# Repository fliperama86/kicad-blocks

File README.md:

# kicad-blocks

Reusable KiCad design blocks shared across projects.

Each subdirectory is a single block: a self-contained schematic snippet
(plus optional layout, symbols, and footprints) that can be dropped into
any KiCad project as a hierarchical sheet or, in KiCad 9+, registered as
a Design Block library.

## Layout

```
kicad-blocks/
├── README.md
├── <block-name>/
│   ├── README.md                  # what the block is, sheet pins, BOM, gotchas
│   ├── <block-name>.kicad_sch     # the reusable schematic
│   ├── <block-name>.kicad_pcb     # optional preplaced layout
│   ├── symbols/                   # block-specific symbol library (.kicad_sym)
│   └── footprints.pretty/         # block-specific footprints (.kicad_mod)
└── ...
```

A block should expose its interface only via hierarchical sheet pins.
Anything internal (decoupling caps, crystal, regulator) stays inside
the sheet so projects can reuse without re-wiring.

## Two ways to consume a block

### KiCad 9+ Design Block library (preferred)

1. Open KiCad → Preferences → Manage Design Block Libraries.
2. Add a global library: Path = `~/Projects/kicad-blocks`, Nickname = `kicad-blocks`.
3. In the schematic editor, the Design Block panel will list each
   subdirectory as a block. Drop one onto a sheet.

### Hierarchical sheet (KiCad 7/8 fallback)

1. In the schematic editor, Place → Add Hierarchical Sheet.
2. Point the sheet file at `~/Projects/kicad-blocks/<block>/<block>.kicad_sch`.
3. Annotate; per-instance refdes are tracked by KiCad automatically.

## Editing a block

Open the block's own `.kicad_pro` (or the `.kicad_sch` directly) — never
edit the file from inside a consuming project, or KiCad will save a
project-local copy and break the upstream link.

After editing, every project that consumes the block needs an ERC/DRC
re-run and a reannotate; bump the block's README "Revision" line so
downstream consumers know to pull.

## Blocks

- [`RP2354B_core/`](RP2354B_core/README.md) — RP2354B MCU core with
  XOSC, decoupling, RUN/boot circuitry, 1V1 regulator. No external
  flash (RP2354B has 2 MB on-die).

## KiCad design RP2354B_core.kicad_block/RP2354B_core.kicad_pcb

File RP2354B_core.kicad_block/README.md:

# RP2354B_core

Reusable RP2354B (or RP2350B) MCU core block, derived from the official
Raspberry Pi RP2350B Minimal Board reference (RP-006442-DD-2).

The schematic is QFN-80 footprint compatible with both:

- **RP2354B** (preferred) — 2 MB on-die stacked flash, no external QSPI flash needed.
- **RP2350B** — wire an external QSPI flash to the `QSPI_*` sheet pins.

## Status

Schematic v0.1 — pruned from the reference design via the KiCad MCP
server. Still requires a UI pass to:

1. Run ERC and prune dangling wires left behind by the deleted parts
   (USB, breakout headers, mounting holes, flash, buttons).
2. Add hierarchical labels at the boundary (replace power flags and
   former net-to-connector exits with `Hierarchical Label`s matching
   the sheet pin names below).
3. Reannotate (refdes numbers are sparse after deletions).
4. Optionally relocate parts so the remaining circuit fits a tighter
   sheet area before exporting as a Design Block.

## Files

- `RP2354B_core.kicad_pro` / `.kicad_sch` / `.kicad_pcb`
- `MCU_RaspberryPi_RP2350.kicad_sym` — project-local symbol library
  (RP2350_80QFN symbol; same footprint accepts RP2354B).
- `RP2350_80QFN_minimal.pretty/` — project-local footprint library
  (RP2350 QFN-80, crystal, regulator, passives).

The unmodified RPi reference archive used as the starting point lives
in `~/Downloads/RP-008295-DS-1-Minimal-KiCAD rp2350/` (Raspberry Pi
RP-006442-DD-2). Re-import from there if a clean baseline is needed.

## What's inside (post-prune, 46 placed symbols)

- **U1** — RP2350_80QFN (assemble as RP2354B; see U1 properties).
- **U2** — NCP1117-3.3 LDO, VBUS → 3V3 (DNP if consumer feeds 3V3 directly).
- **Y1** — 12 MHz crystal (`ABM8-272-T3`) with `C3`/`C4` 15 pF load caps,
  `R2` biasing, GND-pinned package.
- **L1 / C6 / C7** — 3.3 µH + 4.7 µF LC filter for VREG_VIN.
- **C9 / C10** — 4.7 µF 1V1 bulk.
- **C19** — 10 µF 3V3 bulk.
- **C1 / C5** — 10 µF caps around the regulator.
- **C8, C11–C18, C20, C21, C13** — 100 nF per-supply-pin decoupling.
- **R3** — 33 Ω (VREG bias).
- **R6** — 1 kΩ (RUN pull-up).
- Power flags: `+3V3`, `+1V1`, `VBUS`, `GND`.

## Proposed sheet pin interface

To convert this into a Design Block / hierarchical sheet, the consumer
sees these pins only:

| Group | Sheet Pins | Direction (sub-sheet POV) |
| --- | --- | --- |
| Power in | `VBUS` (optional, into reg), `3V3`, `GND` | input |
| Reset / boot | `RUN`, `BOOTSEL`, `USB_BOOT` | bidirectional |
| Debug | `SWCLK`, `SWDIO` | bidirectional |
| USB | `USB_DP`, `USB_DM` | bidirectional |
| QSPI (PSRAM on RP2354B; flash+PSRAM on RP2350B) | `QSPI_SCK`, `QSPI_CSn`, `QSPI_SD0`–`QSPI_SD3` | bidirectional |
| GPIO | `GPIO0`..`GPIO47` | bidirectional |
| ADC | `ADC_AVDD`, `ADC_GND` | input |

Lock the final list when adding the hierarchical labels in KiCad.

## Revision

- **v0.1 (2026-05-14)** — pruned reference design: deleted USB connector,
  2× 26-pin breakouts, 4× mounting holes, BOOTSEL + RUN push buttons,
  USB 27 Ω series resistors, primary + alt W25Q128JVS flash and their
  decoupling/pull-ups; tagged U1 with MPN/Description properties. ERC
  and hierarchical labels still pending.
- v0 — scaffolding only.

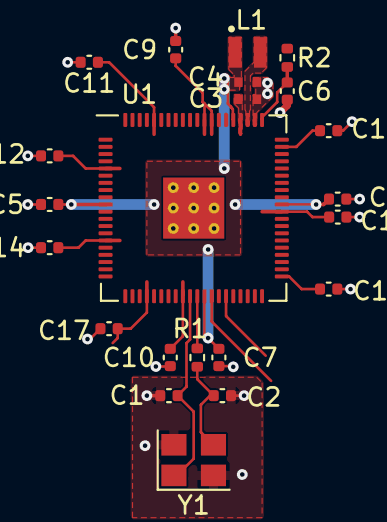
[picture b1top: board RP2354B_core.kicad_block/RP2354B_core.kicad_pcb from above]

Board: 2 copper layers, 22 parts (0 on the bottom side), 8 nets.

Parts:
C1, C2: 15p; C_0402_1005Metric
C3, C4: 4.7u; C_0402_1005Metric_small_pads
C5, C8, C9, C10, C11, C12, C13, C14, C15, C16, C17: 100n; C_0402_1005Metric
C6, C7: 4.7u; C_0402_1005Metric
L1: 3.3u; L_pol_2016
R1: 1k; R_0402_1005Metric
R2: 33; R_0402_1005Metric
U1: RP2350_80QFN; RP2350-QFN-80-1EP_10x10_P0.4mm_EP3.4x3.4mm_ThermalVias
Y1: ABM8-272-T3; Crystal_SMD_3225-4Pin_3.2x2.5mm

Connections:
+1V1: C4.1, C5.1, C7.1, C8.1, L1.1, U1.10 (DVDD), U1.32 (DVDD), U1.51 (DVDD), U1.65 (VREG_FB)
+3V3: C3.1, C9.1, C10.1, C11.1, C12.1, C13.1, C14.1, C15.1, C16.1, C17.1, R2.1, U1.5 (IOVDD), U1.15 (IOVDD), U1.24 (IOVDD), U1.29 (IOVDD), U1.41 (IOVDD), U1.50 (IOVDD), U1.59 (ADC_AVDD), U1.60 (IOVDD), U1.64 (VREG_VIN), U1.68 (USB_OTP_VDD), U1.69 (QSPI_IOVDD), U1.76 (IOVDD)
/VREG_AVDD: C6.1, R2.2, U1.61 (VREG_AVDD)
/VREG_LX: L1.2, U1.63 (VREG_LX)
/XIN: C1.1, U1.30 (XIN), Y1.1
/XOUT: R1.1, U1.31 (XOUT)
GND: C1.2, C2.2, C3.2, C4.2, C5.2, C6.2, C7.2, C8.2, C9.2, C10.2, C11.2, C12.2, C13.2, C14.2, C15.2, C16.2, C17.2, U1.62 (VREG_PGND), U1.81 (GND), Y1.2, Y1.4
unnamed: C2.1, R1.2, Y1.3

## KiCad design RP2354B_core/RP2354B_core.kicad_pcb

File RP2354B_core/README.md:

# RP2354B_core

Reusable RP2354B (or RP2350B) MCU core block, derived from the official
Raspberry Pi RP2350B Minimal Board reference (RP-006442-DD-2).

The schematic is QFN-80 footprint compatible with both:

- **RP2354B** (preferred) — 2 MB on-die stacked flash, no external QSPI flash needed.
- **RP2350B** — wire an external QSPI flash to the `QSPI_*` sheet pins.

## Status

Schematic v0.1 — pruned from the reference design via the KiCad MCP
server. Still requires a UI pass to:

1. Run ERC and prune dangling wires left behind by the deleted parts
   (USB, breakout headers, mounting holes, flash, buttons).
2. Add hierarchical labels at the boundary (replace power flags and
   former net-to-connector exits with `Hierarchical Label`s matching
   the sheet pin names below).
3. Reannotate (refdes numbers are sparse after deletions).
4. Optionally relocate parts so the remaining circuit fits a tighter
   sheet area before exporting as a Design Block.

## Files

- `RP2354B_core.kicad_pro` / `.kicad_sch` / `.kicad_pcb`
- `MCU_RaspberryPi_RP2350.kicad_sym` — project-local symbol library
  (RP2350_80QFN symbol; same footprint accepts RP2354B).
- `RP2350_80QFN_minimal.pretty/` — project-local footprint library
  (RP2350 QFN-80, crystal, regulator, passives).
- `_reference_import/` — unmodified copy of the RPi reference archive,
  kept for audit. Delete once the block is locked.

## What's inside (post-prune, 46 placed symbols)

- **U1** — RP2350_80QFN (assemble as RP2354B; see U1 properties).
- **U2** — NCP1117-3.3 LDO, VBUS → 3V3 (DNP if consumer feeds 3V3 directly).
- **Y1** — 12 MHz crystal (`ABM8-272-T3`) with `C3`/`C4` 15 pF load caps,
  `R2` biasing, GND-pinned package.
- **L1 / C6 / C7** — 3.3 µH + 4.7 µF LC filter for VREG_VIN.
- **C9 / C10** — 4.7 µF 1V1 bulk.
- **C19** — 10 µF 3V3 bulk.
- **C1 / C5** — 10 µF caps around the regulator.
- **C8, C11–C18, C20, C21, C13** — 100 nF per-supply-pin decoupling.
- **R3** — 33 Ω (VREG bias).
- **R6** — 1 kΩ (RUN pull-up).
- Power flags: `+3V3`, `+1V1`, `VBUS`, `GND`.

## Proposed sheet pin interface

To convert this into a Design Block / hierarchical sheet, the consumer
sees these pins only:

| Group | Sheet Pins | Direction (sub-sheet POV) |
| --- | --- | --- |
| Power in | `VBUS` (optional, into reg), `3V3`, `GND` | input |
| Reset / boot | `RUN`, `BOOTSEL`, `USB_BOOT` | bidirectional |
| Debug | `SWCLK`, `SWDIO` | bidirectional |
| USB | `USB_DP`, `USB_DM` | bidirectional |
| QSPI (PSRAM on RP2354B; flash+PSRAM on RP2350B) | `QSPI_SCK`, `QSPI_CSn`, `QSPI_SD0`–`QSPI_SD3` | bidirectional |
| GPIO | `GPIO0`..`GPIO47` | bidirectional |
| ADC | `ADC_AVDD`, `ADC_GND` | input |

Lock the final list when adding the hierarchical labels in KiCad.

## Revision

- **v0.1 (2026-05-14)** — pruned reference design: deleted USB connector,
  2× 26-pin breakouts, 4× mounting holes, BOOTSEL + RUN push buttons,
  USB 27 Ω series resistors, primary + alt W25Q128JVS flash and their
  decoupling/pull-ups; tagged U1 with MPN/Description properties. ERC
  and hierarchical labels still pending.
- v0 — scaffolding only.

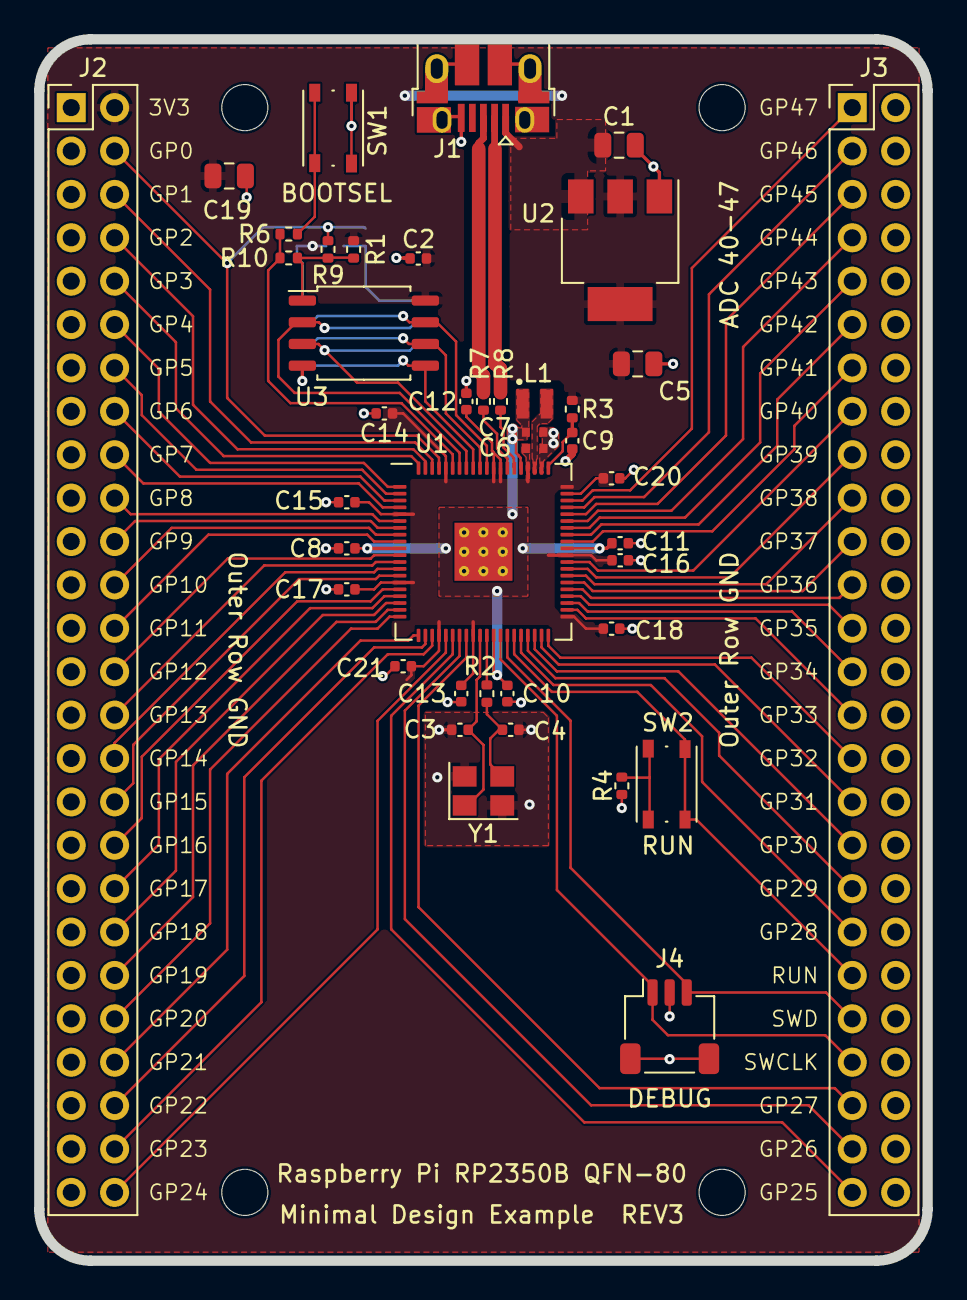
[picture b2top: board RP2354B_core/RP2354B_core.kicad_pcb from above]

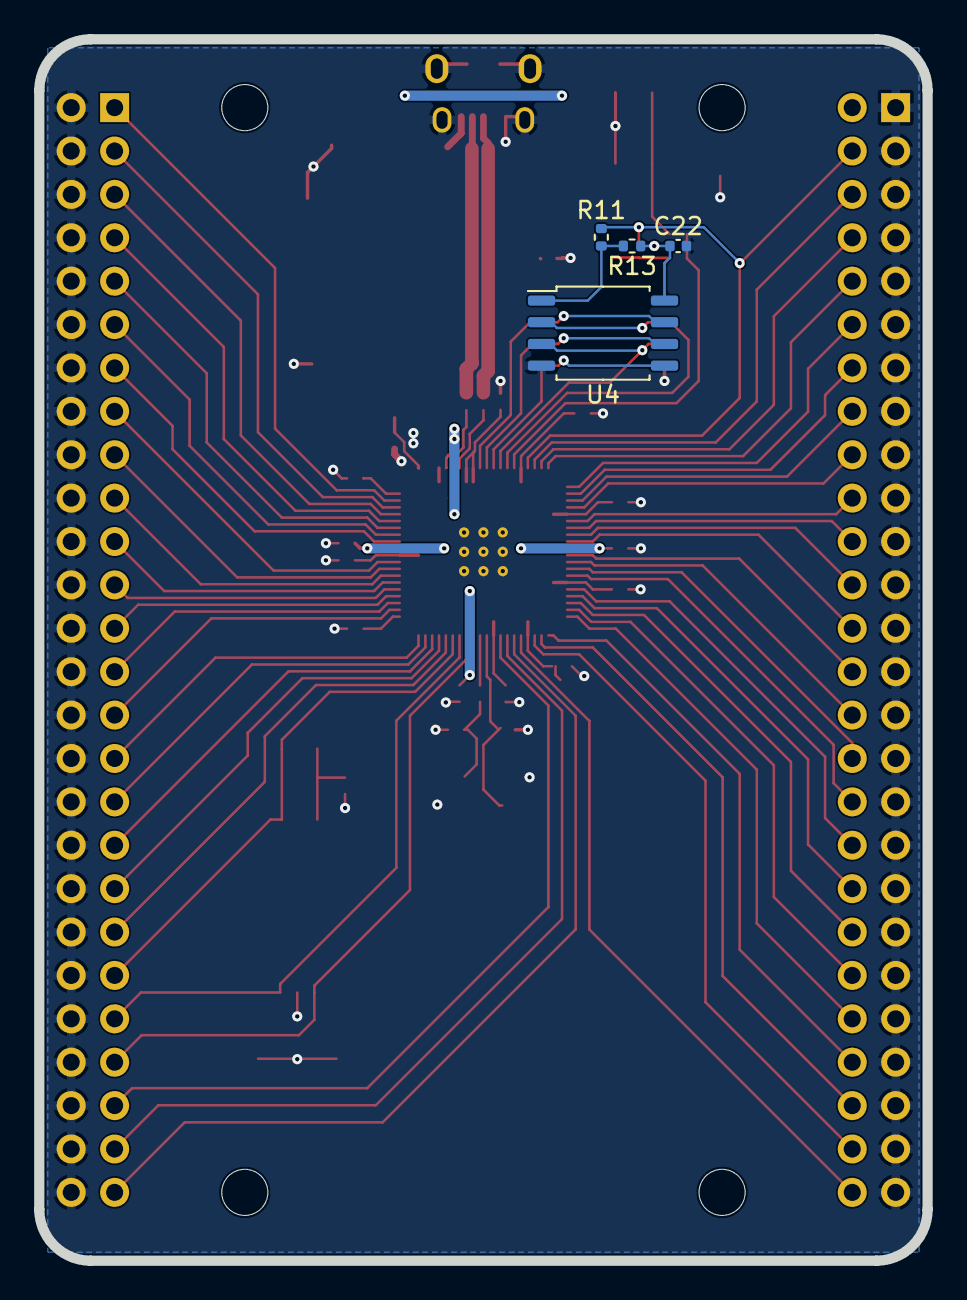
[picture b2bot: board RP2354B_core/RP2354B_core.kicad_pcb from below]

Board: 2 copper layers, 52.0 x 71.5 mm, 49 parts (4 on the bottom side), 74 nets.

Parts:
C1, C5, C19: 10u; C_0805_2012Metric
C2, C8, C11, C12, C13, C14, C15, C16, C17, C18, C20, C21: 100n; C_0402_1005Metric
C3, C4: 15p; C_0402_1005Metric
C6, C7: 4.7u; C_0402_1005Metric_small_pads
C9, C10: 4.7u; C_0402_1005Metric
C22: DNF; C_0402_1005Metric
H1, H2, H3, H4: MountingHole; MountingHole_2.7mm_M2.5
J1: USB_B_Micro; USB_Micro-B_Amphenol_10103594-0001LF_Horizontal
J2, J3: Conn_02x26_Odd_Even; PinHeader_2x26_P2.54mm_Vertical
J4: SM03B-SRSS-TB; JST_SH_SM03B-SRSS-TB_1x03-1MP_P1.00mm_Horizontal
L1: 3.3u; L_pol_2016
R1, R9, R11, R13: DNF; R_0402_1005Metric
R2, R4, R6: 1k; R_0402_1005Metric
R3: 33; R_0402_1005Metric
R7, R8: 27; R_0402_1005Metric
R10: 0; R_0402_1005Metric
SW1, SW2: SW_Push; SW_Push_1P1T_NO_Vertical_Wuerth_434133025816
U1: RP2350_80QFN; RP2350-QFN-80-1EP_10x10_P0.4mm_EP3.4x3.4mm_ThermalVias
U2: NCP1117-3.3_SOT223; SOT-223-3_TabPin2
U3: W25Q128JVS; SOIC-8_5.23x5.23mm_P1.27mm
U4: DNF; SOIC-8_5.23x5.23mm_P1.27mm
Y1: ABM8-272-T3; Crystal_SMD_3225-4Pin_3.2x2.5mm

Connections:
+1V1: C7.1, C8.1, C10.1, C11.1, L1.1, U1.10 (DVDD), U1.32 (DVDD), U1.51 (DVDD), U1.65 (VREG_FB)
+3V3: C2.1, C5.1, C6.1, C12.1, C13.1, C14.1, C15.1, C16.1, C17.1, C18.1, C19.1, C20.1, C21.1, C22.1, J2.2, R1.1, R3.1, R13.1, U1.5 (IOVDD), U1.15 (IOVDD), U1.24 (IOVDD), U1.29 (IOVDD), U1.41 (IOVDD), U1.50 (IOVDD), U1.59 (ADC_AVDD), U1.60 (IOVDD), U1.64 (VREG_VIN), U1.68 (USB_OTP_VDD), U1.69 (QSPI_IOVDD), U1.76 (IOVDD), U2.2 (VO), U3.8 (VCC), U4.8 (VCC)
/FLASH2_SS: R11.2, R13.2, U4.1 (~CS)
/FLASH_SS: R1.2, R9.2, R10.2, U3.1 (~CS)
/GPIO0: J2.4, R9.1, R11.1, U1.77 (GPIO0)
/GPIO1: J2.6, U1.78 (GPIO1)
/GPIO2: J2.8, U1.79 (GPIO2)
/GPIO3: J2.10, U1.80 (GPIO3)
/GPIO4: J2.12, U1.1 (GPIO4)
/GPIO5: J2.14, U1.2 (GPIO5)
/GPIO6: J2.16, U1.3 (GPIO6)
/GPIO7: J2.18, U1.4 (GPIO7)
/GPIO8: J2.20, U1.6 (GPIO8)
/GPIO9: J2.22, U1.7 (GPIO9)
/GPIO10: J2.24, U1.8 (GPIO10)
/GPIO11: J2.26, U1.9 (GPIO11)
/GPIO12: J2.28, U1.11 (GPIO12)
/GPIO13: J2.30, U1.12 (GPIO13)
/GPIO14: J2.32, U1.13 (GPIO14)
/GPIO15: J2.34, U1.14 (GPIO15)
/GPIO16: J2.36, U1.16 (GPIO16)
/GPIO17: J2.38, U1.17 (GPIO17)
/GPIO18: J2.40, U1.18 (GPIO18)
/GPIO19: J2.42, U1.19 (GPIO19)
/GPIO20: J2.44, U1.20 (GPIO20)
/GPIO21: J2.46, U1.21 (GPIO21)
/GPIO22: J2.48, U1.22 (GPIO22)
/GPIO23: J2.50, U1.23 (GPIO23)
/GPIO24: J2.52, U1.25 (GPIO24)
/GPIO25: J3.51, U1.26 (GPIO25)
/GPIO26: J3.49, U1.27 (GPIO26)
/GPIO27: J3.47, U1.28 (GPIO27)
/GPIO28: J3.39, U1.36 (GPIO28)
/GPIO29: J3.37, U1.37 (GPIO29)
/GPIO30: J3.35, U1.38 (GPIO30)
/GPIO31: J3.33, U1.39 (GPIO31)
/GPIO32: J3.31, U1.40 (GPIO32)
/GPIO33: J3.29, U1.42 (GPIO33)
/GPIO34: J3.27, U1.43 (GPIO34)
/GPIO35: J3.25, U1.44 (GPIO35)
/GPIO36: J3.23, U1.45 (GPIO36)
/GPIO37: J3.21, U1.46 (GPIO37)
/GPIO38: J3.19, U1.47 (GPIO38)
/GPIO39: J3.17, U1.48 (GPIO39)
/GPIO40_ADC0: J3.15, U1.49 (GPIO40_ADC0)
/GPIO41_ADC1: J3.13, U1.52 (GPIO41_ADC1)
/GPIO42_ADC2: J3.11, U1.53 (GPIO42_ADC2)
/GPIO43_ADC3: J3.9, U1.54 (GPIO43_ADC3)
/GPIO44_ADC4: J3.7, U1.55 (GPIO44_ADC4)
/GPIO45_ADC5: J3.5, U1.56 (GPIO45_ADC5)
/GPIO46_ADC6: J3.3, U1.57 (GPIO46_ADC6)
/GPIO47_ADC7: J3.1, U1.58 (GPIO47_ADC7)
/QSPI_SCLK: U1.71 (QSPI_SCLK), U3.6 (CLK), U4.6 (CLK)
/QSPI_SD0: U1.72 (QSPI_SD0), U3.5 (DI(IO0)), U4.5 (DI(IO0))
/QSPI_SD1: U1.74 (QSPI_SD1), U3.2 (DO(IO1)), U4.2 (DO(IO1))
/QSPI_SD2: U1.73 (QSPI_SD2), U3.3 (IO2), U4.3 (IO2)
/QSPI_SD3: U1.70 (QSPI_SD3), U3.7 (IO3), U4.7 (IO3)
/QSPI_SS: R6.1, R10.1, U1.75 (QSPI_SS)
/RUN: J3.41, SW2.2, U1.35 (RUN)
/SWCLK: J3.45, J4.1, U1.33 (SWCLK)
/SWD: J3.43, J4.3, U1.34 (SWD)
/USB_D+: J1.3 (D+), R7.1
/USB_D-: J1.2 (D-), R8.1
/VREG_AVDD: C9.1, R3.2, U1.61 (VREG_AVDD)
/VREG_LX: L1.2, U1.63 (VREG_LX)
/XIN: C3.1, U1.30 (XIN), Y1.1
/XOUT: R2.1, U1.31 (XOUT)
/~USB_BOOT: R6.2, SW1.2
GND: C1.2, C2.2, C3.2, C4.2, C5.2, C6.2, C7.2, C8.2, C9.2, C10.2, C11.2, C12.2, C13.2, C14.2, C15.2, C16.2, C17.2, C18.2, C19.2, C20.2, C21.2, C22.2, J1.5 (GND), J1.6 (Shield), J2.1, J2.3, J2.5, J2.7, J2.9, J2.11, J2.13, J2.15, J2.17, J2.19, J2.21, J2.23, J2.25, J2.27, J2.29, J2.31, J2.33, J2.35, J2.37, J2.39, J2.41, J2.43, J2.45, J2.47, J2.49, J2.51, J3.2, J3.4, J3.6, J3.8, J3.10, J3.12, J3.14, J3.16, J3.18, J3.20, J3.22, J3.24, J3.26, J3.28, J3.30, J3.32, J3.34, J3.36, J3.38, J3.40, J3.42, J3.44, J3.46, J3.48, J3.50, J3.52, J4.2, J4.MP (MountPin), R4.2, SW1.1, U1.62 (VREG_PGND), U1.81 (GND), U2.1 (GND), U3.4 (GND), U4.4 (GND), Y1.2, Y1.4
unnamed: C4.1, R2.2, Y1.3
unnamed: R4.1, SW2.1
unnamed: R8.2, U1.66 (USB_DM)
unnamed: R7.2, U1.67 (USB_DP)
VBUS: C1.1, J1.1 (VBUS), U2.3 (VI)

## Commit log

2026-05-14 Scaffold kicad-blocks repo with RP2354B_core block stub
2026-05-14 RP2354B_core v0.1: prune RPi reference to MCU+reg+XOSC+decoupling
    Imported the Raspberry Pi RP2350B Minimal Board archive and stripped it
    down to just the reusable core: deleted USB, breakout headers, mounting
    holes, BOOTSEL/RUN buttons, USB 27R series, and both W25Q128JVS flash
    chips (primary + alt) plus their decoupling/pull-ups. Tagged U1 with MPN
    and Description noting RP2354B (preferred, integrated 2MB flash) or
    RP2350B (with external QSPI flash). 81 symbols -> 46. ERC pass and
2026-05-14 Drop _reference_import (had nested .history git repo); add to .gitignore
2026-05-14 README: drop _reference_import refs, point at Downloads source
2026-05-16 RP2354B_core v0.2: rename dir as kicad_block, add hierarchical labels
    KiCad design block scanner requires <name>.kicad_block as the
    directory suffix, so renamed RP2354B_core/ -> RP2354B_core.kicad_block/.
    Library URI in design-block-lib-table points at the parent kicad-blocks/
    directory; KiCad now picks up the block from any project.
    Added 53 hierarchical labels on U1 boundary nets so the block exposes
    a real sheet-pin interface:
2026-05-19 Renumber block components sequentially (C1..C17, R1..R2)
    Closes refdes gaps that caused duplicate footprints when importing the
    block PCB into parent projects via re-link by refdes.
2026-05-19 Add CLAUDE.md with design block authoring + import workflow
    Captures the gotchas learned the hard way: .kicad_block dir naming,
    sequential refdes, sch/PCB sync via F8, ERC severity overrides for
    standalone block ERC, and the paste-special + F8 re-link recipe for
    importing a block's routed PCB into a parent project.
